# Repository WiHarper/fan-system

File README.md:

# fan-system

Alan Bailey, Landon Doughty, Sean Drzewiczewski, and Wilson Harper contributed equally to this project.

- Access the documentation [here](https://docs.google.com/document/d/1xmE79On1B4ku6Sfotu_lNZXdt6c-R4M1_0iMoffMgmM/edit?tab=t.0) (using your `@rice.edu` Google Account). 
- To request collaborator privileges, email Wilson Harper using your `@rice.edu` Google Account.

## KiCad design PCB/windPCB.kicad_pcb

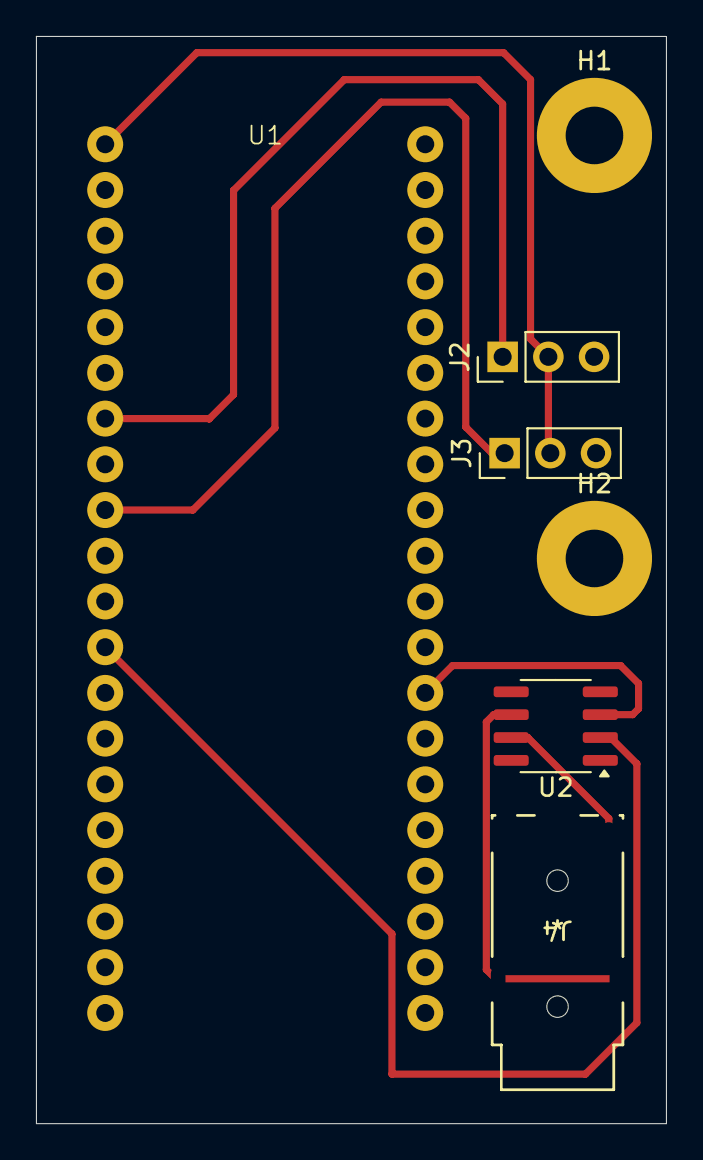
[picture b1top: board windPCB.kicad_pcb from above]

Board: 2 copper layers, 35.0 x 60.4 mm, 7 parts (0 on the bottom side), 5 nets.

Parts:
H1, H2: MountingHole; MountingHole_3.2mm_M3_Pad
J2, J3: Conn_01x03; PinHeader_1x03_P2.54mm_Vertical
J4: 54-00174; TRRS_3.5MM_AUDIO_JACK_54-00174_TEN
U1: ESP_ETH
U2: TC4427xOA; SOIC-8_3.9x4.9mm_P1.27mm

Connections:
+5V: J2.2, J3.2, U1.21 (VBUS)
GND: J2.3, J3.3, U1.3 (GND), U1.8 (GND), U1.13 (GND), U1.18 (GND), U1.23 (GND), U1.28 (GND), U1.33 (GND), U1.38 (GND), U2.3 (GND)
fan: U1.32 (IO15), U2.2 (IN_A)
servo1: J3.1, U1.29 (IO16)
servo2: J2.1, U1.27 (IO17)

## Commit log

2026-03-25 Add web server code
2026-03-27 Implement UDP
2026-04-18 Update for fan PWM
2026-04-18 Add Unity script
2026-05-08 Updated and organized
2026-05-08 Change docs
2026-05-08 Rename folder
2026-05-08 Add contact info
2026-05-08 Improve README.md formatting for documentation access
    Split the documentation access and collaborator request into separate lines for clarity.
2026-05-08 Format email address in README.md
2026-05-08 PCB files
